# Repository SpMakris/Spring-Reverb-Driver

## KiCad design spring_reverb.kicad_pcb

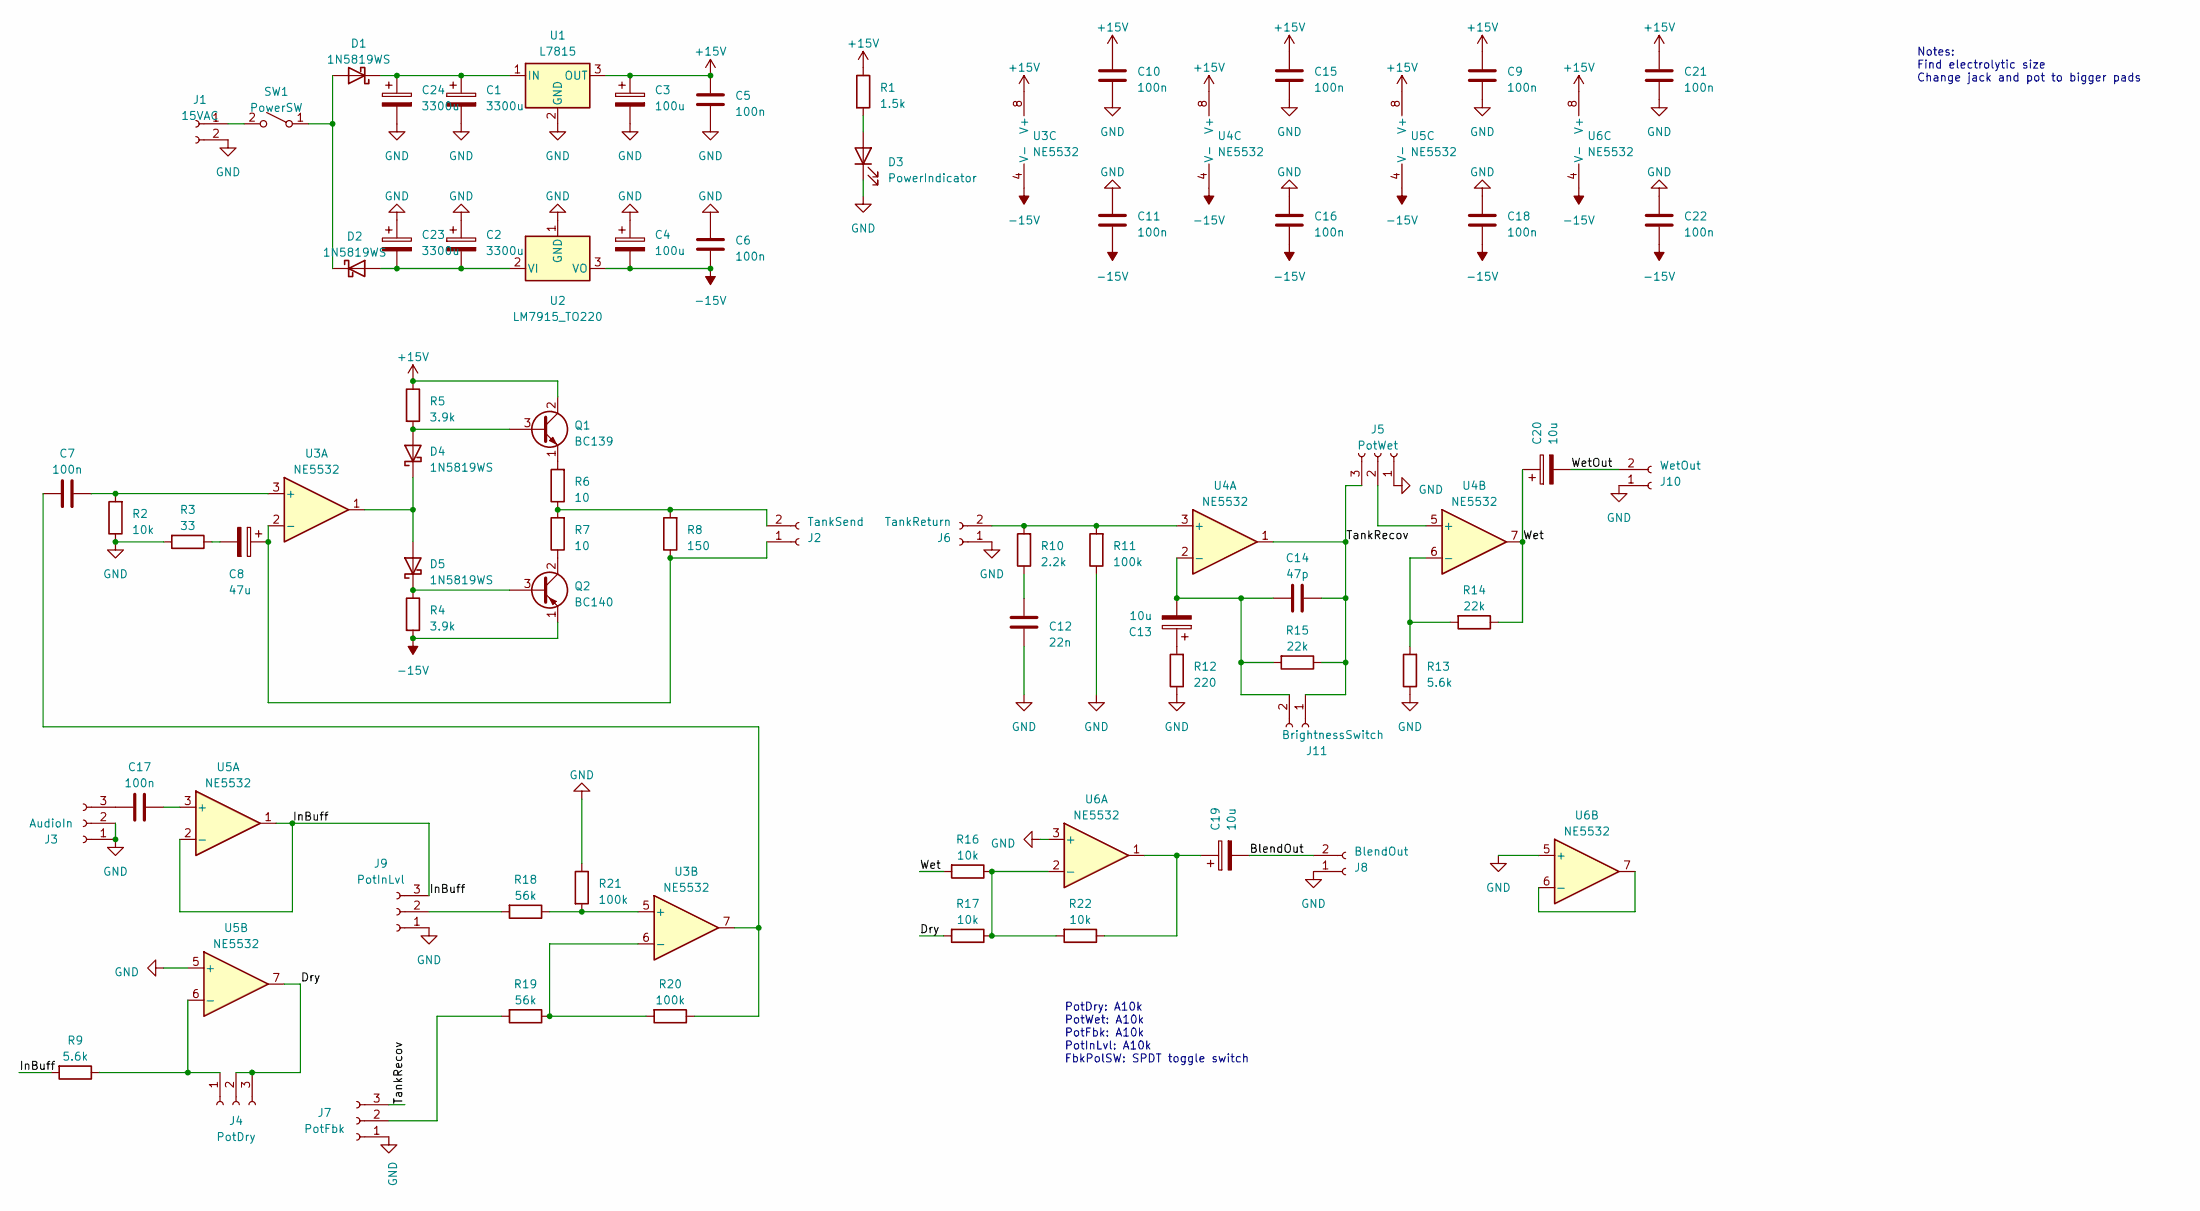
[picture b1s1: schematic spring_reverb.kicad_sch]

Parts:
C1, C2, C23, C24: 3300u; CP_Radial_D18.0mm_P7.50mm
C3, C4: 100u; CP_Radial_D8.0mm_P2.50mm
C5, C6, C7, C9, C10, C11, C15, C16, C17, C18, C21, C22: 100n; C_0603_1608Metric_Pad1.08x0.95mm_HandSolder
C8: 47u; CP_Radial_D8.0mm_P2.50mm
C12: 22n; C_0603_1608Metric_Pad1.08x0.95mm_HandSolder
C13, C19, C20: 10u; CP_Radial_D8.0mm_P2.50mm
C14: 47p; C_0805_2012Metric_Pad1.18x1.45mm_HandSolder
D1, D2, D4, D5: 1N5819WS; D_SOD-323_HandSoldering
D3: PowerIndicator; LED_D5.0mm
J1: 15VAC; 01x02_3mm
J2: TankSend; 01x02_3mm
J3: AudioIn; 01x03_2mm
J4: PotDry; 01x03_2mm
J5: PotWet; 01x03_2mm
J6: TankReturn; 01x02_3mm
J7: PotFbk; 01x03_2mm
J8: BlendOut; 01x02_3mm
J9: PotInLvl; 01x03_2mm
J10: WetOut; 01x02_3mm
J11: BrightnessSwitch; 01x02_3mm
Q1: BC139; SIPAK_Vertical
Q2: BC140; SIPAK_Vertical
R1: 1.5k; R_0603_1608Metric_Pad0.98x0.95mm_HandSolder
R2, R16, R17, R22: 10k; R_0603_1608Metric_Pad0.98x0.95mm_HandSolder
R3: 33; R_0603_1608Metric_Pad0.98x0.95mm_HandSolder
R4, R5: 3.9k; R_0603_1608Metric_Pad0.98x0.95mm_HandSolder
R6, R7: 10; R_0603_1608Metric_Pad0.98x0.95mm_HandSolder
R8: 150; R_0603_1608Metric_Pad0.98x0.95mm_HandSolder
R9, R13: 5.6k; R_0603_1608Metric_Pad0.98x0.95mm_HandSolder
R10: 2.2k; R_0603_1608Metric_Pad0.98x0.95mm_HandSolder
R11, R20, R21: 100k; R_0603_1608Metric_Pad0.98x0.95mm_HandSolder
R12: 220; R_0603_1608Metric_Pad0.98x0.95mm_HandSolder
R14, R15: 22k; R_0603_1608Metric_Pad0.98x0.95mm_HandSolder
R18, R19: 56k; R_0603_1608Metric_Pad0.98x0.95mm_HandSolder
SW1: PowerSW; 01x02_3mm
U1: L7815; TO-220-3_Vertical
U2: LM7915_TO220; TO-220-3_Vertical
U3, U4, U5, U6: NE5532; SOIC-8_3.9x4.9mm_P1.27mm

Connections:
+15V: C3.1, C5.1, C9.1, C10.1, C15.1, C21.1, Q1.2 (C), R1.1, R5.1, U1.3 (OUT), U3.8 (V+), U4.8 (V+), U5.8 (V+), U6.8 (V+)
-15V: C4.2, C6.2, C11.2, C16.2, C18.2, C22.2, Q2.1 (E), R4.2, U2.3 (VO), U3.4 (V-), U4.4 (V-), U5.4 (V-), U6.4 (V-)
/BlendOut: C19.2, J8.2
/Dry: J4.2, J4.3, R17.2, U5.7
/InBuff: J9.3, R9.2, U5.1, U5.2 (-)
/TankRecov: C14.1, J5.3, J7.3, J11.1, R15.1, U4.1
/Wet: C20.1, R14.1, R16.2, U4.7
/WetOut: C20.2, J10.2
GND: C1.2, C2.1, C3.2, C4.1, C5.2, C6.1, C9.2, C10.2, C11.1, C12.1, C15.2, C16.1, C18.1, C21.2, C22.1, C23.1, C24.2, D3.1 (K), J1.2, J3.1, J3.2, J5.1, J6.1, J7.1, J8.1, J9.1, J10.1, R2.1, R3.2, R11.1, R12.1, R13.1, R21.1, U1.2 (GND), U2.1 (GND), U5.5 (+), U6.3 (+), U6.5 (+)
unnamed: C7.2, R20.1, U3.7
unnamed: C8.2, R3.1
unnamed: C12.2, R10.1
unnamed: C13.1, R12.2
unnamed: C19.1, R22.1, U6.1
unnamed: D1.2 (A), D2.1 (K), SW1.1 (A)
unnamed: C1.1, C24.1, D1.1 (K), U1.1 (IN)
unnamed: C2.2, C23.2, D2.2 (A), U2.2 (VI)
unnamed: D3.2 (A), R1.2
unnamed: D4.2 (A), Q1.3 (B), R5.2
unnamed: D4.1 (K), D5.2 (A), U3.1
unnamed: D5.1 (K), Q2.3 (B), R4.1
unnamed: J1.1, SW1.2 (B)
unnamed: C8.1, J2.1, R8.1, U3.2 (-)
unnamed: J2.2, R6.1, R7.2, R8.2
unnamed: C17.1, J3.3
unnamed: J4.1, R9.1, U5.6 (-)
unnamed: J5.2, U4.5 (+)
unnamed: J6.2, R10.2, R11.2, U4.3 (+)
unnamed: J7.2, R19.2
unnamed: J9.2, R18.2
unnamed: C13.2, C14.2, J11.2, R15.2, U4.2 (-)
unnamed: Q1.1 (E), R6.2
unnamed: Q2.2 (C), R7.1
unnamed: C7.1, R2.2, U3.3 (+)
unnamed: R18.1, R21.2, U3.5 (+)
unnamed: R19.1, R20.2, U3.6 (-)
unnamed: R13.2, R14.2, U4.6 (-)
unnamed: C17.2, U5.3 (+)
unnamed: R16.1, R17.1, R22.2, U6.2 (-)
unnamed: U6.6 (-), U6.7

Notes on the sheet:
PotDry: A10k PotWet: A10k PotFbk: A10k PotInLvl: A10k FbkPolSW: SPDT toggle switch
Notes: Find electrolytic size Change jack and pot to bigger pads

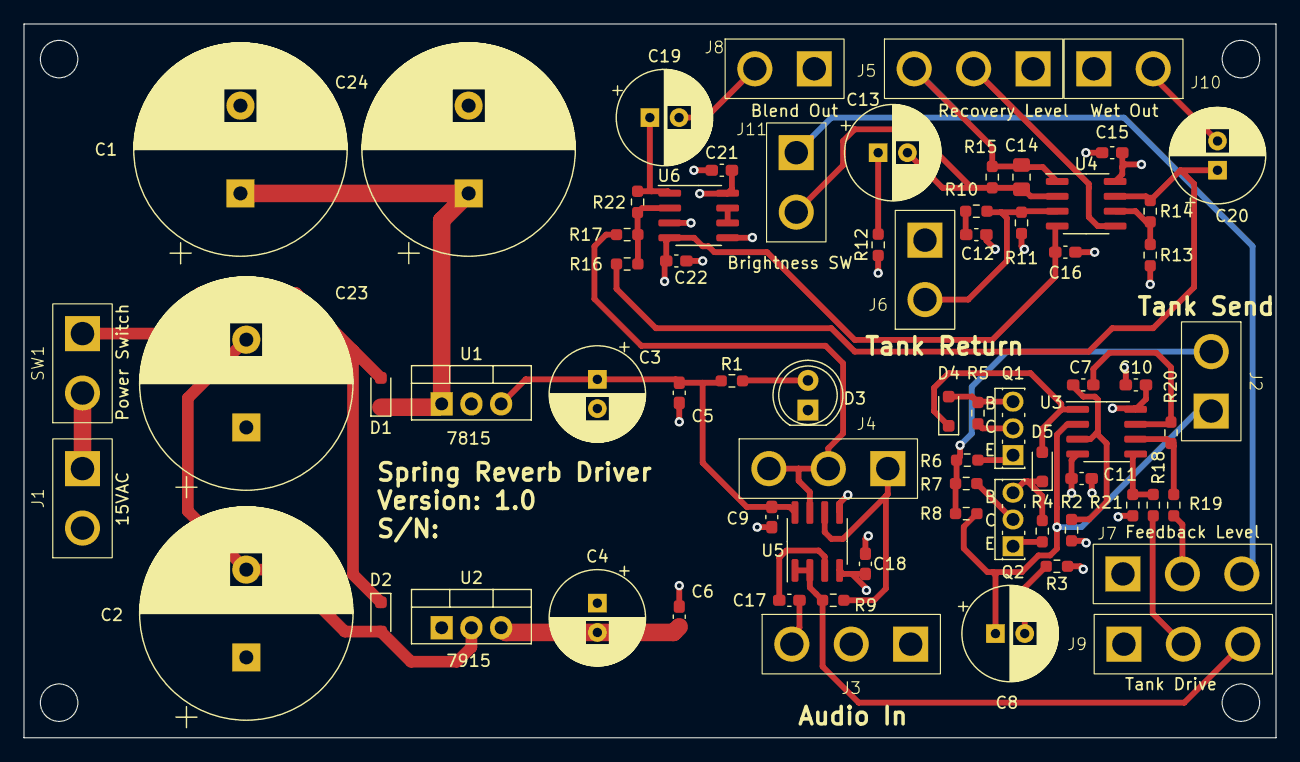
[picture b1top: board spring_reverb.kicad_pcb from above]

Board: 4 copper layers, 107.0 x 61.0 mm, 71 parts (0 on the bottom side), 40 nets.
